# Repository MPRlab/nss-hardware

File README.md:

# Nucleo Solenoid Shield - Hardware

This repository contains the KiCad files for the Nucleo Solenoid Shield.

Each version of the shield (A/B/C) can drive 25 solenoids from different sets of IO pins. The exact pin names can be found [here](https://docs.google.com/spreadsheets/d/1F1l6_GBWTKrIMixAlwO8Ikh-0bkGv4sUIIGNAyeHcug/edit?usp=sharing). 

The board is powered from a 4-pin ATX connector. The two contacts closest to the latch are the supply voltage and the two pins away from the latch are ground.

Next to the main power input is a secondary input for 5V to the Nucleo. The pin closest to the ATX connectore is 5V in, the middle pin is ground, and the third pin is connected to the solenoid supply voltage.

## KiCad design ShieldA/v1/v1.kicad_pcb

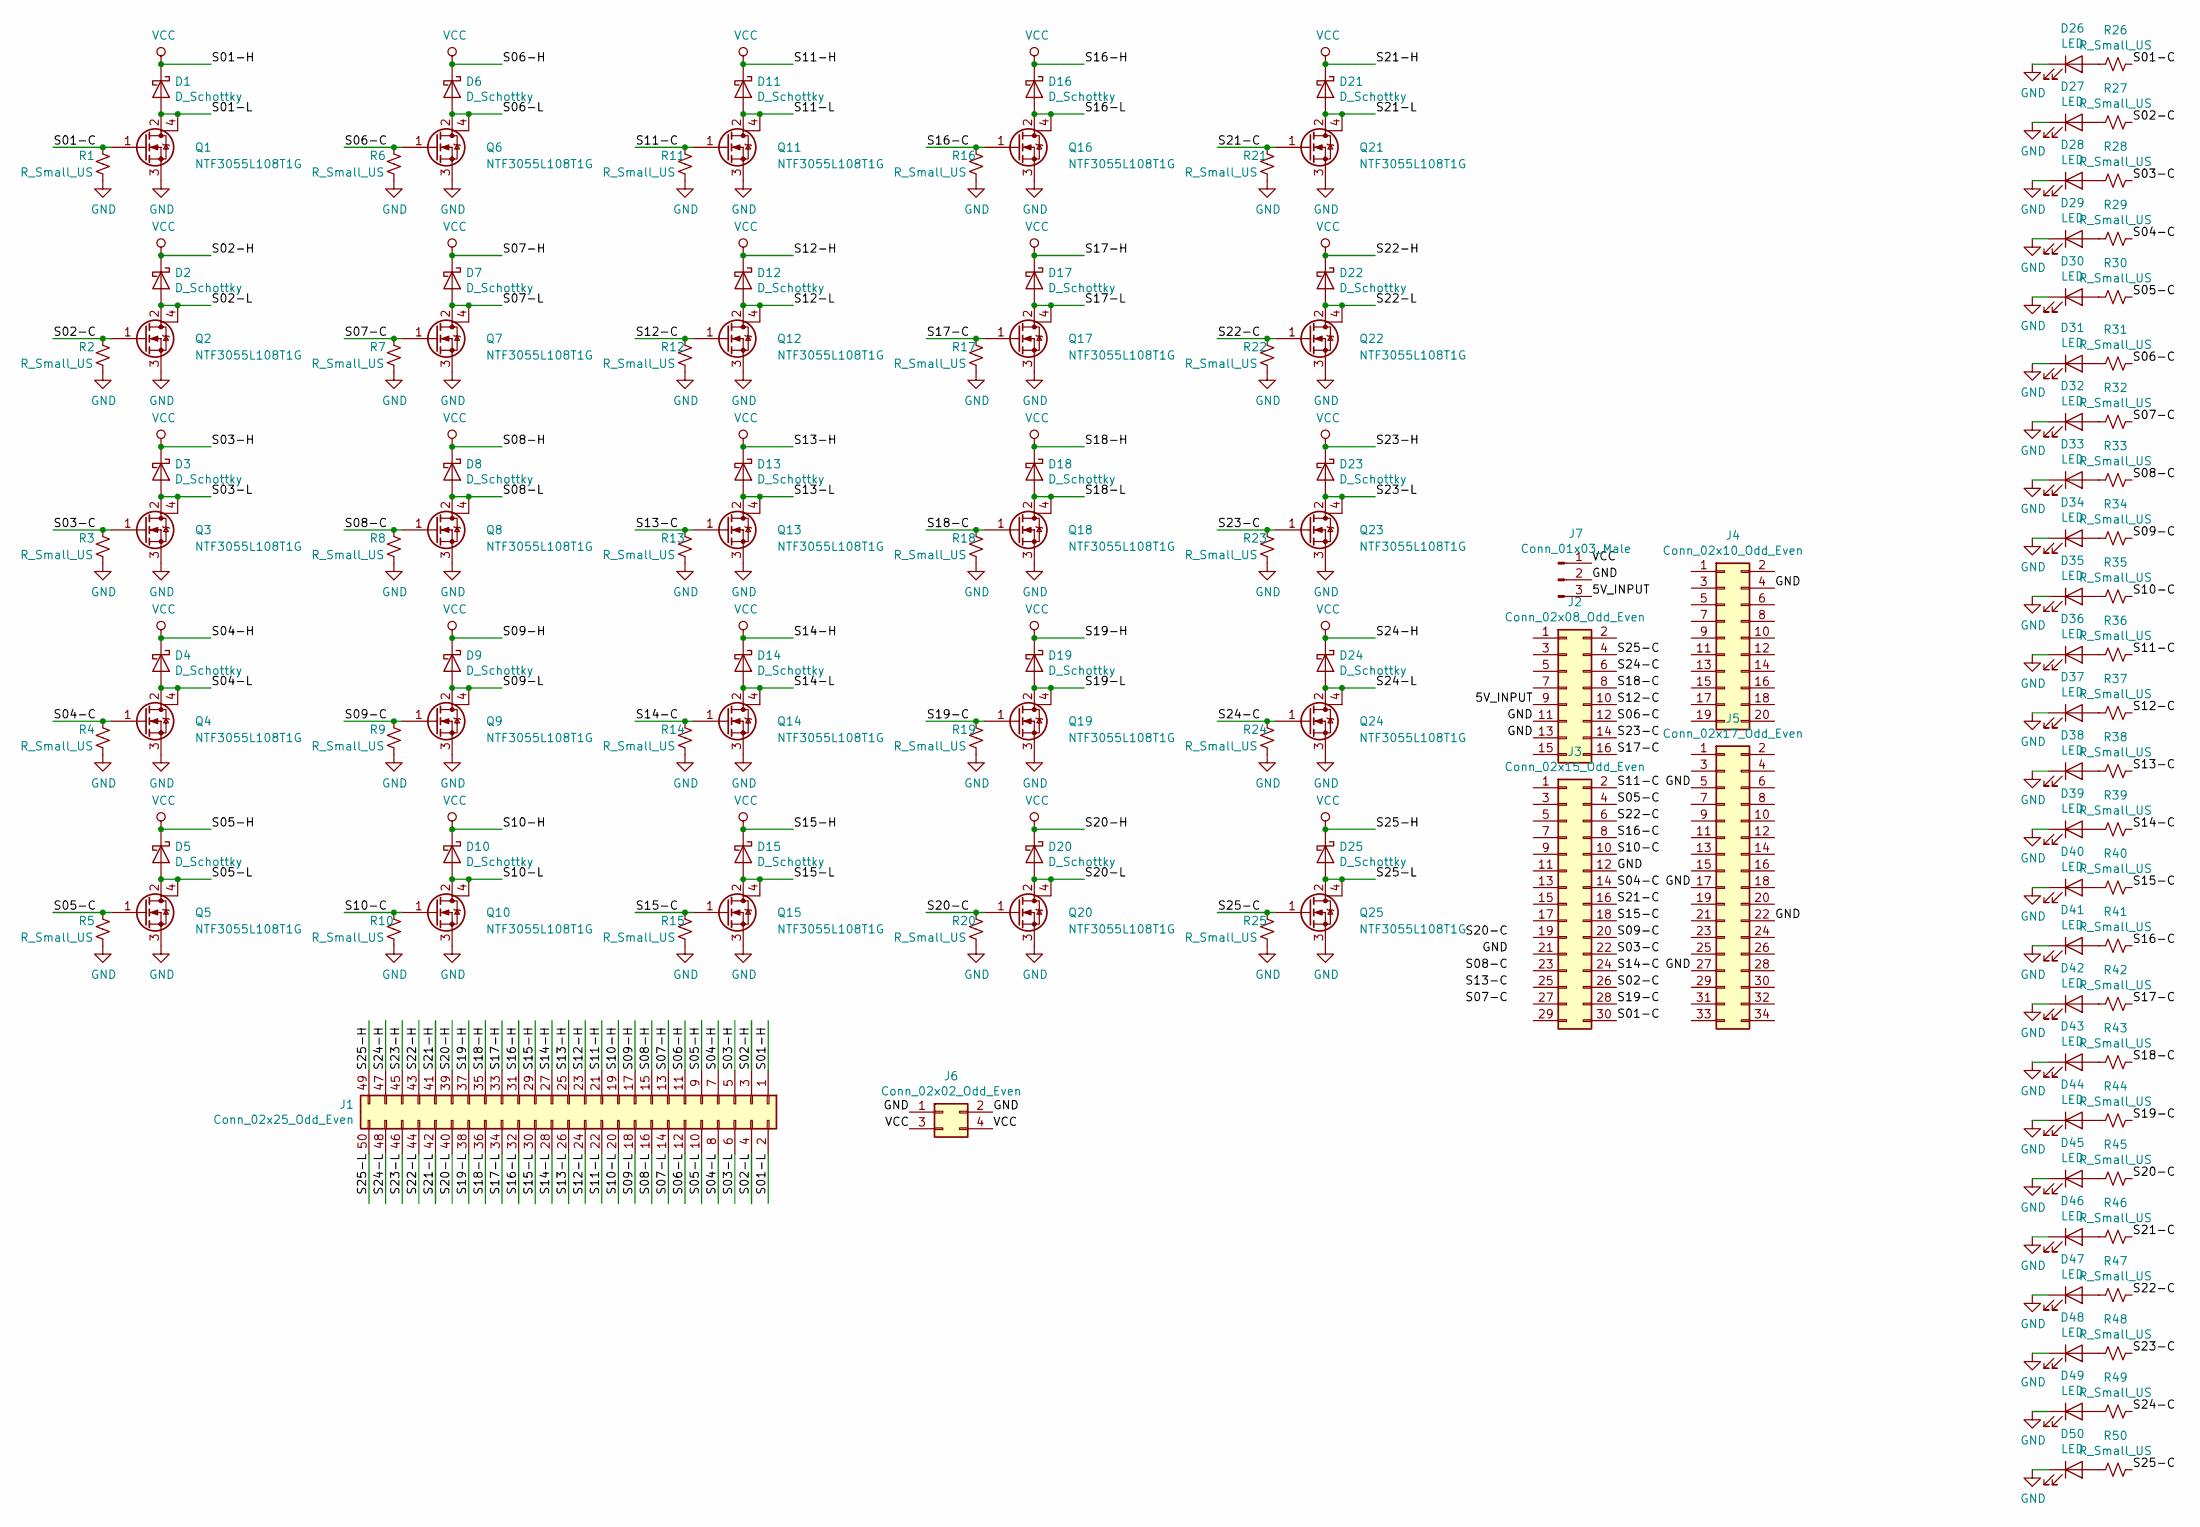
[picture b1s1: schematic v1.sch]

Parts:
D1, D2, D3, D4, D5, D6, D7, D8, D9, D10, D11, D12, D13, D14, D15, D16, D17, D18, D19, D20, D21, D22, D23, D24, D25: D_Schottky; D_SOD-123F
D26, D27, D28, D29, D30, D31, D32, D33, D34, D35, D36, D37, D38, D39, D40, D41, D42, D43, D44, D45, D46, D47, D48, D49, D50: LED; LED_0805_2012Metric_Pad1.15x1.40mm_HandSolder
J1: Conn_02x25_Odd_Even; PinHeader_2x25_P2.54mm_Horizontal
J2: Conn_02x08_Odd_Even; PinHeader_2x08_P2.54mm_Vertical
J3: Conn_02x15_Odd_Even; PinHeader_2x15_P2.54mm_Vertical
J4: Conn_02x10_Odd_Even; PinHeader_2x10_P2.54mm_Vertical
J5: Conn_02x17_Odd_Even; PinHeader_2x17_P2.54mm_Vertical
J6: Conn_02x02_Odd_Even; Molex_Mini-Fit_Jr_5569-04A2_2x02_P4.20mm_Horizontal
J7: Conn_01x03_Male; PinHeader_1x03_P2.54mm_Horizontal
Q1, Q2, Q3, Q4, Q5, Q6, Q7, Q8, Q9, Q10, Q11, Q12, Q13, Q14, Q15, Q16, Q17, Q18, Q19, Q20, Q21, Q22, Q23, Q24, Q25: NTF3055L108T1G; SOT-223
R1, R2, R3, R4, R5, R6, R7, R8, R9, R10, R11, R12, R13, R14, R15, R16, R17, R18, R19, R20, R21, R22, R23, R24, R25, R26, R27, R28, R29, R30, R31, R32, R33, R34, R35, R36, R37, R38, R39, R40, R41, R42, R43, R44, R45, R46, R47, R48, R49, R50: R_Small_US; R_0805_2012Metric_Pad1.15x1.40mm_HandSolder

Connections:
/5V_INPUT: J2.9, J7.3
/S01-C: J3.30, Q1.1 (G), R1.1, R26.1
/S01-L: D1.2 (A), J1.2, Q1.2 (D), Q1.4 (D)
/S02-C: J3.26, Q2.1 (G), R2.1, R27.1
/S02-L: D2.2 (A), J1.4, Q2.2 (D), Q2.4 (D)
/S03-C: J3.22, Q3.1 (G), R3.1, R28.1
/S03-L: D3.2 (A), J1.6, Q3.2 (D), Q3.4 (D)
/S04-C: J3.14, Q4.1 (G), R4.1, R29.1
/S04-L: D4.2 (A), J1.8, Q4.2 (D), Q4.4 (D)
/S05-C: J3.4, Q5.1 (G), R5.1, R30.1
/S05-L: D5.2 (A), J1.10, Q5.2 (D), Q5.4 (D)
/S06-C: J2.12, Q6.1 (G), R6.1, R31.1
/S06-L: D6.2 (A), J1.12, Q6.2 (D), Q6.4 (D)
/S07-C: Q7.1 (G), R7.1, R32.1
/S07-L: D7.2 (A), J1.14, Q7.2 (D), Q7.4 (D)
/S08-C: Q8.1 (G), R8.1, R33.1
/S08-L: D8.2 (A), J1.16, Q8.2 (D), Q8.4 (D)
/S09-C: J3.20, Q9.1 (G), R9.1, R34.1
/S09-L: D9.2 (A), J1.18, Q9.2 (D), Q9.4 (D)
/S10-C: J3.10, Q10.1 (G), R10.1, R35.1
/S10-L: D10.2 (A), J1.20, Q10.2 (D), Q10.4 (D)
/S11-C: J3.2, Q11.1 (G), R11.1, R36.1
/S11-L: D11.2 (A), J1.22, Q11.2 (D), Q11.4 (D)
/S12-C: J2.10, Q12.1 (G), R12.1, R37.1
/S12-L: D12.2 (A), J1.24, Q12.2 (D), Q12.4 (D)
/S13-C: Q13.1 (G), R13.1, R38.1
/S13-L: D13.2 (A), J1.26, Q13.2 (D), Q13.4 (D)
/S14-C: J3.24, Q14.1 (G), R14.1, R39.1
/S14-L: D14.2 (A), J1.28, Q14.2 (D), Q14.4 (D)
/S15-C: J3.18, Q15.1 (G), R15.1, R40.1
/S15-L: D15.2 (A), J1.30, Q15.2 (D), Q15.4 (D)
/S16-C: J3.8, Q16.1 (G), R16.1, R41.1
/S16-L: D16.2 (A), J1.32, Q16.2 (D), Q16.4 (D)
/S17-C: J2.16, Q17.1 (G), R17.1, R42.1
/S17-L: D17.2 (A), J1.34, Q17.2 (D), Q17.4 (D)
/S18-C: J2.8, Q18.1 (G), R18.1, R43.1
/S18-L: D18.2 (A), J1.36, Q18.2 (D), Q18.4 (D)
/S19-C: J3.28, Q19.1 (G), R19.1, R44.1
/S19-L: D19.2 (A), J1.38, Q19.2 (D), Q19.4 (D)
/S20-C: Q20.1 (G), R20.1, R45.1
/S20-L: D20.2 (A), J1.40, Q20.2 (D), Q20.4 (D)
/S21-C: J3.16, Q21.1 (G), R21.1, R46.1
/S21-L: D21.2 (A), J1.42, Q21.2 (D), Q21.4 (D)
/S22-C: J3.6, Q22.1 (G), R22.1, R47.1
/S22-L: D22.2 (A), J1.44, Q22.2 (D), Q22.4 (D)
/S23-C: J2.14, Q23.1 (G), R23.1, R48.1
/S23-L: D23.2 (A), J1.46, Q23.2 (D), Q23.4 (D)
/S24-C: J2.6, Q24.1 (G), R24.1, R49.1
/S24-L: D24.2 (A), J1.48, Q24.2 (D), Q24.4 (D)
/S25-C: J2.4, Q25.1 (G), R25.1, R50.1
/S25-L: D25.2 (A), J1.50, Q25.2 (D), Q25.4 (D)
GND: D26.1 (K), D27.1 (K), D28.1 (K), D29.1 (K), D30.1 (K), D31.1 (K), D32.1 (K), D33.1 (K), D34.1 (K), D35.1 (K), D36.1 (K), D37.1 (K), D38.1 (K), D39.1 (K), D40.1 (K), D41.1 (K), D42.1 (K), D43.1 (K), D44.1 (K), D45.1 (K), D46.1 (K), D47.1 (K), D48.1 (K), D49.1 (K), D50.1 (K), J2.11, J2.13, J3.12, J4.4, J5.5, J5.17, J5.22, J5.27, J6.1, J6.2, J7.2, Q1.3 (S), Q2.3 (S), Q3.3 (S), Q4.3 (S), Q5.3 (S), Q6.3 (S), Q7.3 (S), Q8.3 (S), Q9.3 (S), Q10.3 (S), Q11.3 (S), Q12.3 (S), Q13.3 (S), Q14.3 (S), Q15.3 (S), Q16.3 (S), Q17.3 (S), Q18.3 (S), Q19.3 (S), Q20.3 (S), Q21.3 (S), Q22.3 (S), Q23.3 (S), Q24.3 (S), Q25.3 (S), R1.2, R2.2, R3.2, R4.2, R5.2, R6.2, R7.2, R8.2, R9.2, R10.2, R11.2, R12.2, R13.2, R14.2, R15.2, R16.2, R17.2, R18.2, R19.2, R20.2, R21.2, R22.2, R23.2, R24.2, R25.2
unnamed: D26.2 (A), R26.2
unnamed: D27.2 (A), R27.2
unnamed: D28.2 (A), R28.2
unnamed: D29.2 (A), R29.2
unnamed: D30.2 (A), R30.2
unnamed: D31.2 (A), R31.2
unnamed: D32.2 (A), R32.2
unnamed: D33.2 (A), R33.2
unnamed: D34.2 (A), R34.2
unnamed: D35.2 (A), R35.2
unnamed: D36.2 (A), R36.2
unnamed: D37.2 (A), R37.2
unnamed: D38.2 (A), R38.2
unnamed: D39.2 (A), R39.2
unnamed: D40.2 (A), R40.2
unnamed: D41.2 (A), R41.2
unnamed: D42.2 (A), R42.2
unnamed: D43.2 (A), R43.2
unnamed: D44.2 (A), R44.2
unnamed: D45.2 (A), R45.2
unnamed: D46.2 (A), R46.2
unnamed: D47.2 (A), R47.2
unnamed: D48.2 (A), R48.2
unnamed: D49.2 (A), R49.2
unnamed: D50.2 (A), R50.2
VCC: D1.1 (K), D2.1 (K), D3.1 (K), D4.1 (K), D5.1 (K), D6.1 (K), D7.1 (K), D8.1 (K), D9.1 (K), D10.1 (K), D11.1 (K), D12.1 (K), D13.1 (K), D14.1 (K), D15.1 (K), D16.1 (K), D17.1 (K), D18.1 (K), D19.1 (K), D20.1 (K), D21.1 (K), D22.1 (K), D23.1 (K), D24.1 (K), D25.1 (K), J1.1, J1.3, J1.5, J1.7, J1.9, J1.11, J1.13, J1.15, J1.17, J1.19, J1.21, J1.23, J1.25, J1.27, J1.29, J1.31, J1.33, J1.35, J1.37, J1.39, J1.41, J1.43, J1.45, J1.47, J1.49, J6.3, J6.4, J7.1

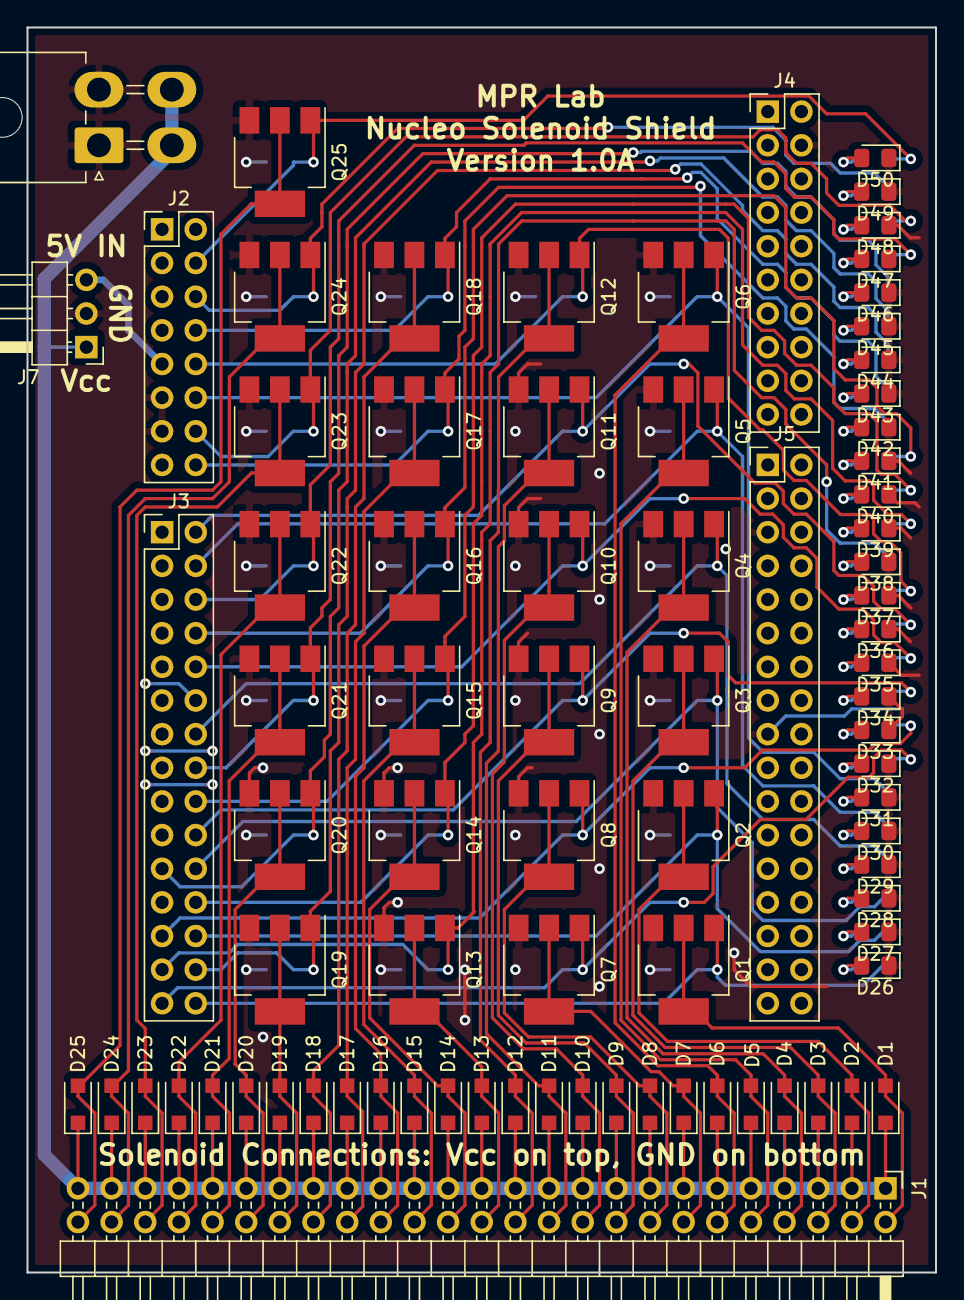
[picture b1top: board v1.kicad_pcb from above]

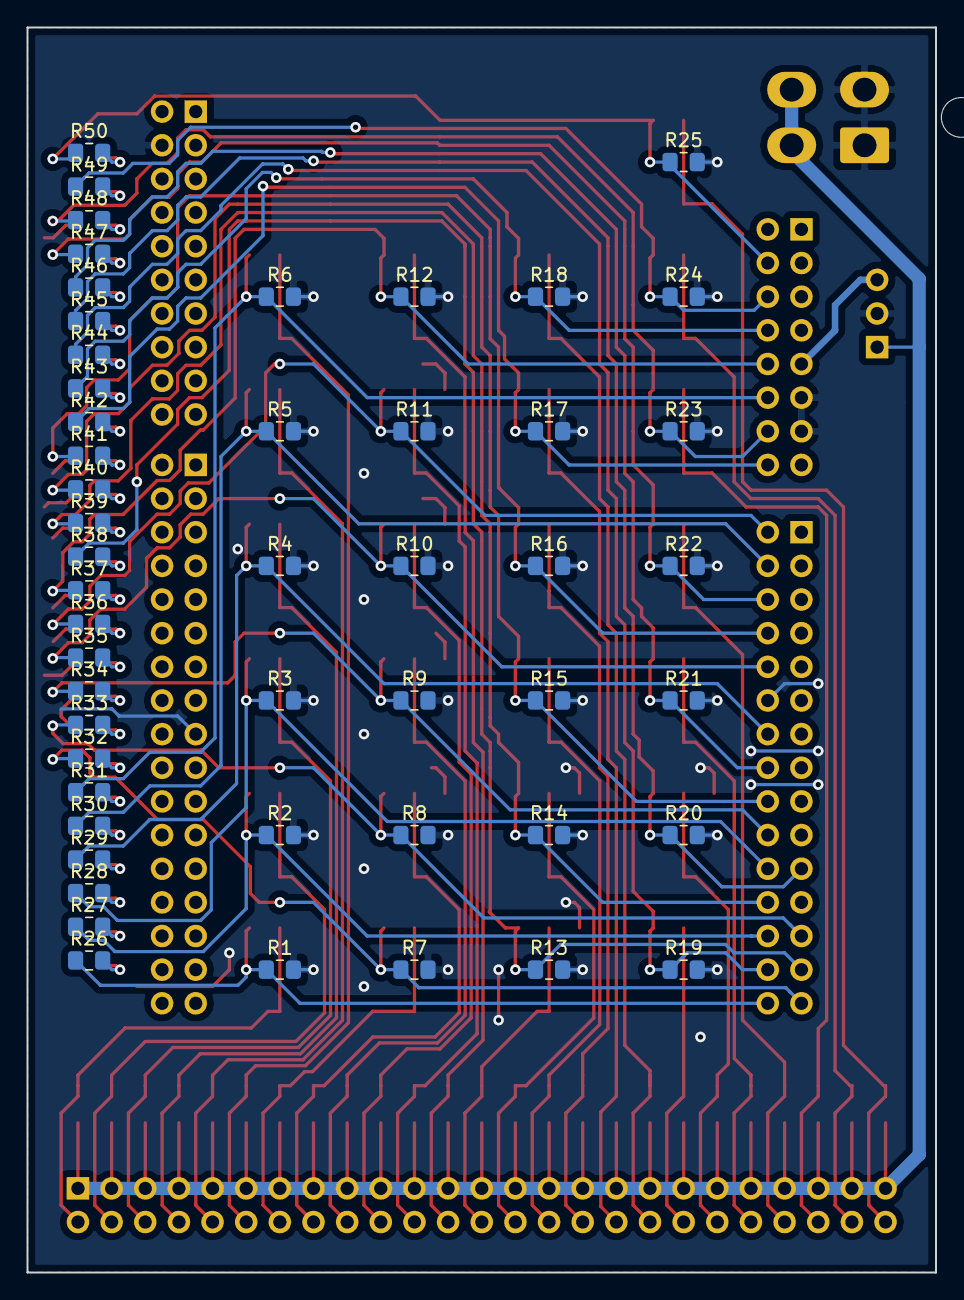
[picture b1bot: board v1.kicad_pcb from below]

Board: 2 copper layers, 68.6 x 94.0 mm, 132 parts (50 on the bottom side), 78 nets.
